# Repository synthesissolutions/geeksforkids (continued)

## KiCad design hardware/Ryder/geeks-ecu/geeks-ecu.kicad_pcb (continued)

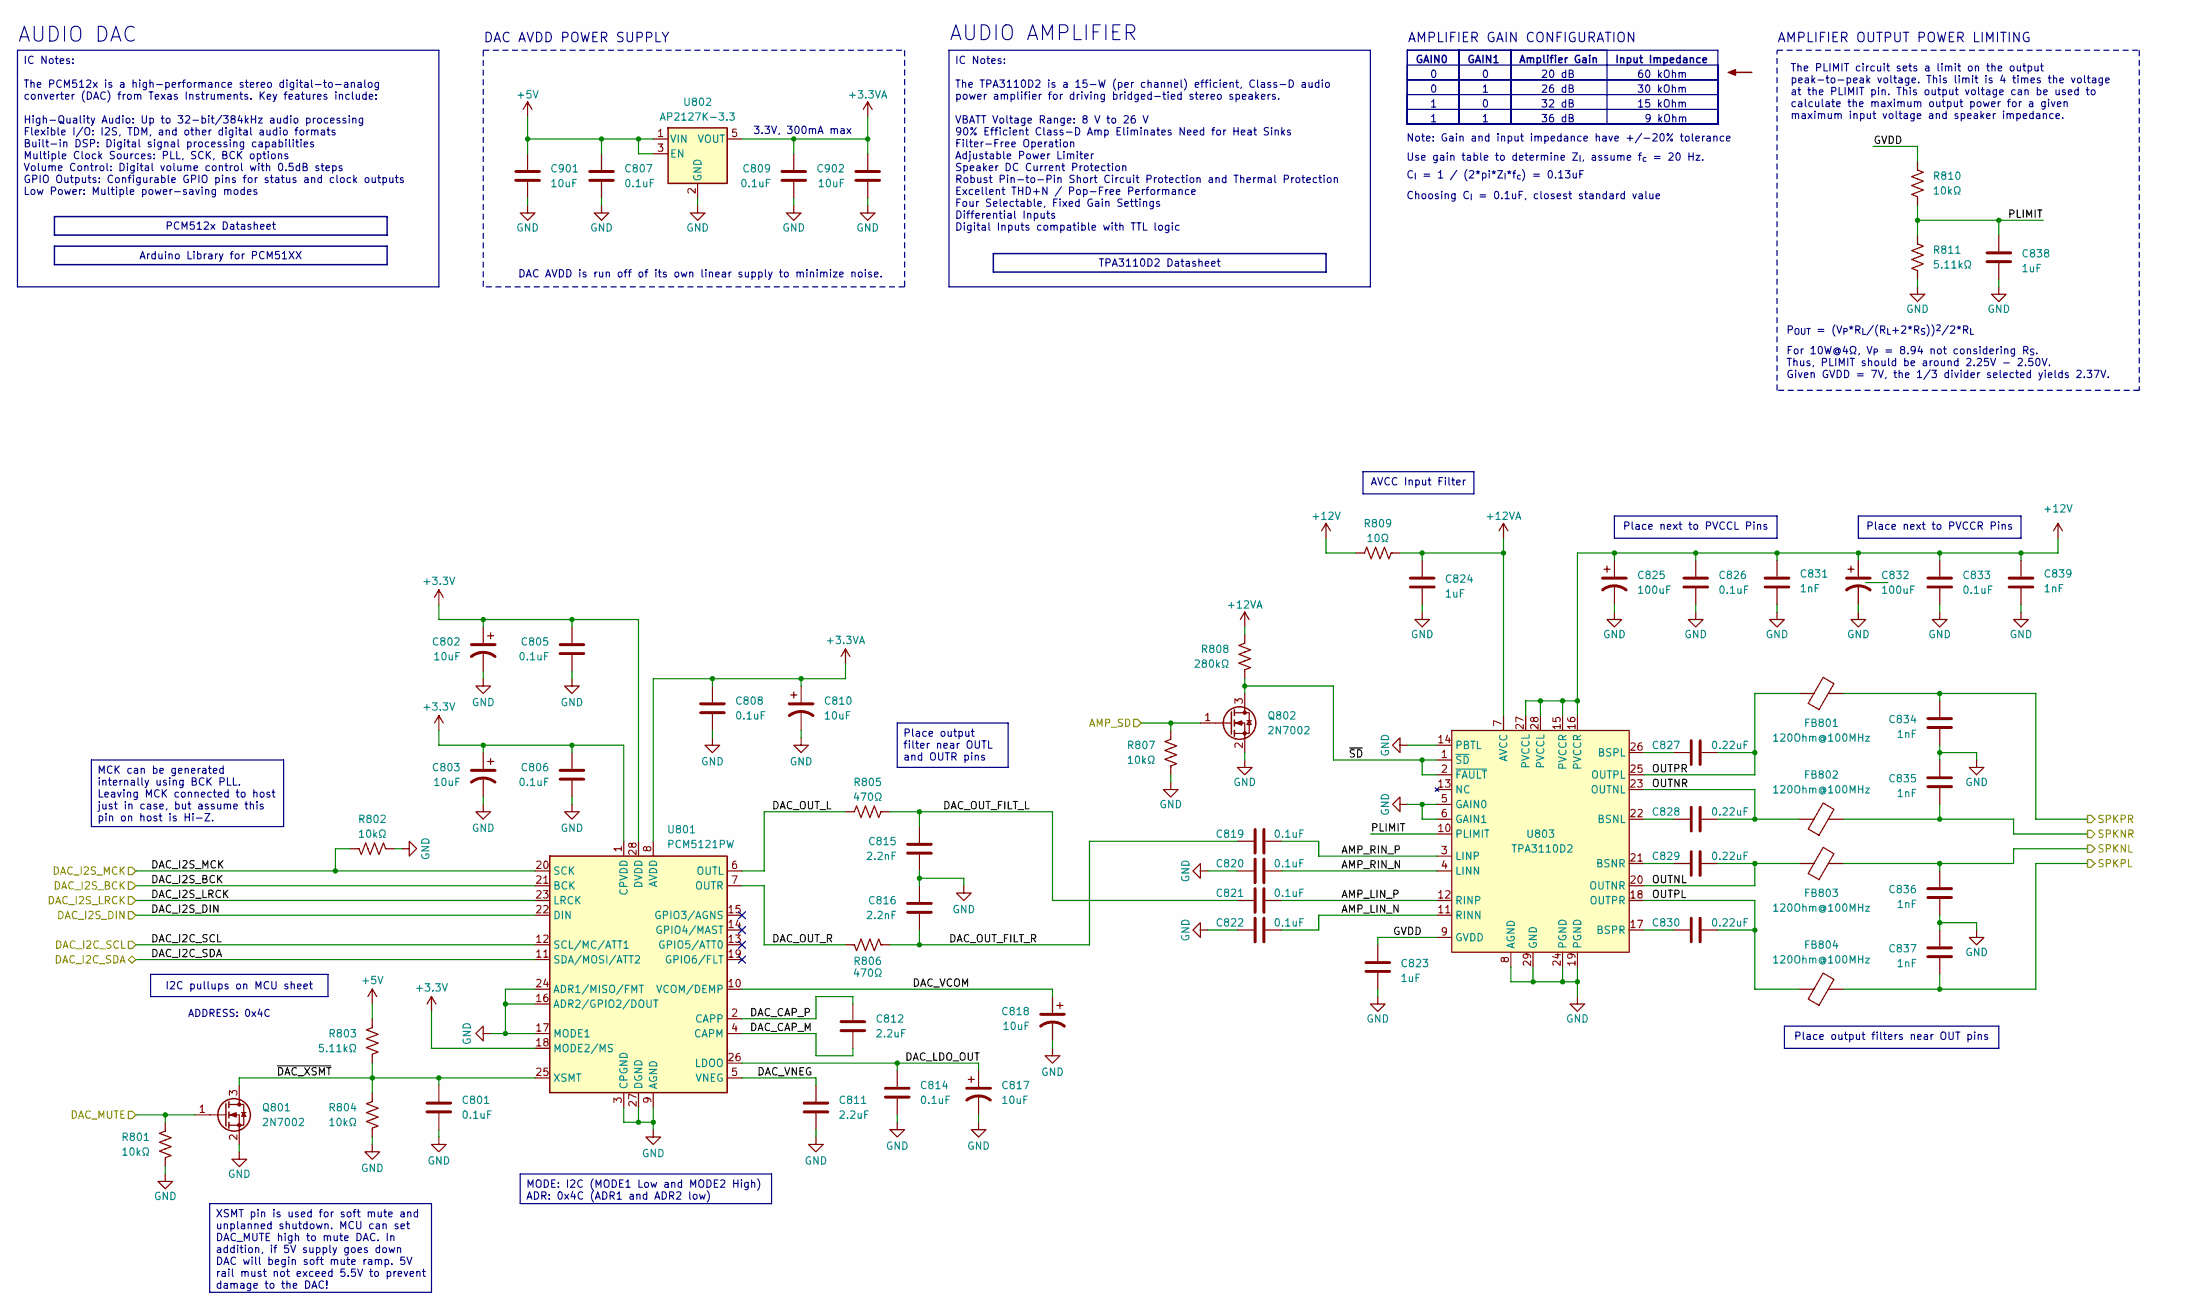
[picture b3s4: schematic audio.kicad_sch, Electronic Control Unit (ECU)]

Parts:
C801, C805, C806, C807, C808, C809, C814, C826, C833: 0.1uF; C_0603_1608Metric; MPN C14663
C802, C803, C810, C817, C818: 10uF; CP_Elec_4x5.4; MPN C72485
C811, C812: 2.2uF; C_0805_2012Metric; MPN C19110
C815, C816: 2.2nF; C_0603_1608Metric; MPN C77033
C819, C820, C821, C822: 0.1uF; C_1206_3216Metric; MPN C97946
C823, C824, C838: 1uF; C_0603_1608Metric; MPN C5199872
C825, C832: 100uF; CP_Radial_D6.3mm_P2.50mm; MPN C47891
C827, C828, C829, C830: 0.22uF; C_1206_3216Metric; MPN C464977
C831, C839: 1nF; C_0603_1608Metric; MPN C106205
C834, C835, C836, C837: 1nF; C_0603_1608Metric; MPN C77026
C901, C902: 10uF; C_0805_2012Metric; MPN C2932476
FB801, FB802, FB803, FB804: 120Ohm@100MHz; L_1206_3216Metric; MPN C3011219
Q801, Q802: 2N7002; SOT-23; MPN C22446827
R801, R802, R804, R807, R810: 10kΩ; R_0603_1608Metric; MPN C25804
R803, R811: 5.11kΩ; R_0603_1608Metric; MPN C23067
R805, R806: 470Ω; R_0603_1608Metric; MPN C23179
R808: 280kΩ; R_0603_1608Metric; MPN C22970
R809: 10Ω; R_0603_1608Metric; MPN C22859
U801: PCM5121PW; TSSOP-28_4.4x9.7mm_P0.65mm; MPN C2651652
U802: AP2127K-3.3; SOT-23-5; MPN C156285
U803: TPA3110D2; HTSSOP-28-1EP_4.4x9.7mm_P0.65mm_EP3.4x9.5mm_Mask2.4x6.17mm_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; MPN C30132

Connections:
+5V: C807.1, C901.2, R803.1, U802.1 (VIN), U802.3 (EN); also elsewhere on the board
+12V: C825.1, C826.1, C831.1, C832.1, C833.1, C839.1, R809.1, U803.15 (PVCCR), U803.16 (PVCCR), U803.27 (PVCCL), U803.28 (PVCCL); also elsewhere on the board
+12VA: C824.2, R808.1, R809.2, U803.7 (AVCC)
/AMP_SD: Q802.1 (G), R807.1; also elsewhere on the board
/Audio/AMP_LIN_N: C822.1, U803.11 (RINN)
/Audio/AMP_LIN_P: C821.1, U803.12 (RINP)
/Audio/AMP_RIN_N: C820.1, U803.4 (LINN)
/Audio/AMP_RIN_P: C819.1, U803.3 (LINP)
/Audio/DAC_CAP_M: C812.2, U801.4 (CAPM)
/Audio/DAC_CAP_P: C812.1, U801.2 (CAPP)
/Audio/DAC_I2S_MCK: R802.2, U801.20 (SCK)
/Audio/DAC_LDO_OUT: C814.1, C817.1, U801.26 (LDOO)
/Audio/DAC_OUT_FILT_L: C815.1, C821.2, R805.2
/Audio/DAC_OUT_FILT_R: C816.2, C819.2, R806.2
/Audio/DAC_OUT_L: R805.1, U801.6 (OUTL)
/Audio/DAC_OUT_R: R806.1, U801.7 (OUTR)
/Audio/DAC_VCOM: C818.1, U801.10 (VCOM/DEMP)
/Audio/DAC_VNEG: C811.1, U801.5 (VNEG)
/Audio/GVDD: C823.2, R810.1, U803.9 (GVDD)
/Audio/OUTNL: C829.1, FB803.1, U803.20 (OUTNR)
/Audio/OUTNR: C828.1, FB802.1, U803.23 (OUTNL)
/Audio/OUTPL: C830.1, FB804.1, U803.18 (OUTPR)
/Audio/OUTPR: C827.1, FB801.1, U803.25 (OUTPL)
/Audio/PLIMIT: C838.2, R810.2, R811.1, U803.10 (PLIMIT)
/Audio/~DAC_XSMT: C801.1, Q801.3 (D), R803.2, R804.1, U801.25 (XSMT)
/Audio/~SD: Q802.3 (D), R808.2, U803.1 (~SD), U803.2 (~FAULT)
/DAC_I2C_SCL: U801.12 (SCL/MC/ATT1); also elsewhere on the board
/DAC_I2C_SDA: U801.11 (SDA/MOSI/ATT2); also elsewhere on the board
/DAC_I2S_BCK: U801.21 (BCK); also elsewhere on the board
/DAC_I2S_DIN: U801.22 (DIN); also elsewhere on the board
/DAC_I2S_LRCK: U801.23 (LRCK); also elsewhere on the board
/DAC_MUTE: Q801.1 (G), R801.1; also elsewhere on the board
/SPKNL: C836.1, FB803.2; also elsewhere on the board
/SPKNR: C835.2, FB802.2; also elsewhere on the board
/SPKPL: C837.2, FB804.2; also elsewhere on the board
/SPKPR: C834.1, FB801.2; also elsewhere on the board
GND: C801.2, C802.2, C803.2, C805.2, C806.2, C807.2, C808.2, C809.2, C810.2, C811.2, C814.2, C815.2, C816.1, C817.2, C818.2, C820.2, C822.2, C823.1, C824.1, C825.2, C826.2, C831.2, C832.2, C833.2, C834.2, C835.1, C836.2, C837.1, C838.1, C839.2, C901.1, C902.1, Q801.2 (S), Q802.2 (S), R801.2, R802.1, R804.2, R807.2, R811.2, U801.3 (CPGND), U801.9 (AGND), U801.16 (ADR2/GPIO2/DOUT), U801.17 (MODE1), U801.24 (ADR1/MISO/FMT), U801.27 (DGND), U802.2 (GND), U803.5 (GAIN0), U803.6 (GAIN1), U803.8 (AGND), U803.14 (PBTL), U803.19 (PGND), U803.24 (PGND), U803.29 (GND); also elsewhere on the board
unnamed: C828.2, U803.22 (BSNL)
unnamed: C829.2, U803.21 (BSNR)
unnamed: C827.2, U803.26 (BSPL)
unnamed: C830.2, U803.17 (BSPR)

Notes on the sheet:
For 10W@4Ω, V_{P} = 8.94 not considering R_{S}. Thus, PLIMIT should be around 2.25V - 2.50V. Given GVDD = 7V, the 1/3 divider selected yields 2.37V.
30 kOhm
AMPLIFIER GAIN CONFIGURATION
AUDIO AMPLIFIER
20 dB
3.3V, 300mA max
GAIN1
Use gain table to determine Z_{I}, assume f_{c} = 20 Hz.
Input Impedance
15 kOhm
AMPLIFIER OUTPUT POWER LIMITING
DAC AVDD POWER SUPPLY
C_{I} = 1 / (2*pi*Z_{I}*f_{c}) = 0.13uF
Note: Gain and input impedance have +/-20% tolerance
DAC AVDD is run off of its own linear supply to minimize noise.
GAIN0
Amplifier Gain
ADDRESS: 0x4C
36 dB
Choosing C_{I} = 0.1uF, closest standard value
26 dB
P_{OUT} = (V_{P}*R_{L}/(R_{L}+2*R_{S}))^{2}/2*R_{L}
AUDIO DAC
60 kOhm
32 dB
9 kOhm
IC Notes: The TPA3110D2 is a 15-W (per channel) efficient, Class-D audio power amplifier for driving bridged-tied stereo speakers. VBATT Voltage Range: 8 V to 26 V 90% Efficient Class-D Amp Eliminates Need for Heat Sinks Filter-Free Operation Adjustable Power Limiter Speaker DC Current Protection R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
TPA3110D2 Datasheet
Place next to PVCCL Pins
The PLIMIT circuit sets a limit on the output peak-to-peak voltage. This limit is 4 times the voltage at the PLIMIT pin. This output voltage can be used to calculate the maximum output power for a given maximum input voltage and speaker impedance.
Place next to PVCCR Pins
MODE: I2C (MODE1 Low and MODE2 High) ADR: 0x4C (ADR1 and ADR2 low)
Arduino Library for PCM51XX
MCK can be generated internally using BCK PLL. Leaving MCK connected to host just in case, but assume this pin on host is Hi-Z.
Place output filter near OUTL and OUTR pins
PCM512x Datasheet
AVCC Input Filter
I2C pullups on MCU sheet
XSMT pin is used for soft mute and unplanned shutdown. MCU can set DAC_MUTE high to mute DAC. In addition, if 5V supply goes down DAC will begin soft mute ramp. 5V rail must not exceed 5.5V to prevent damage to the DAC!
Place output filters near OUT pins

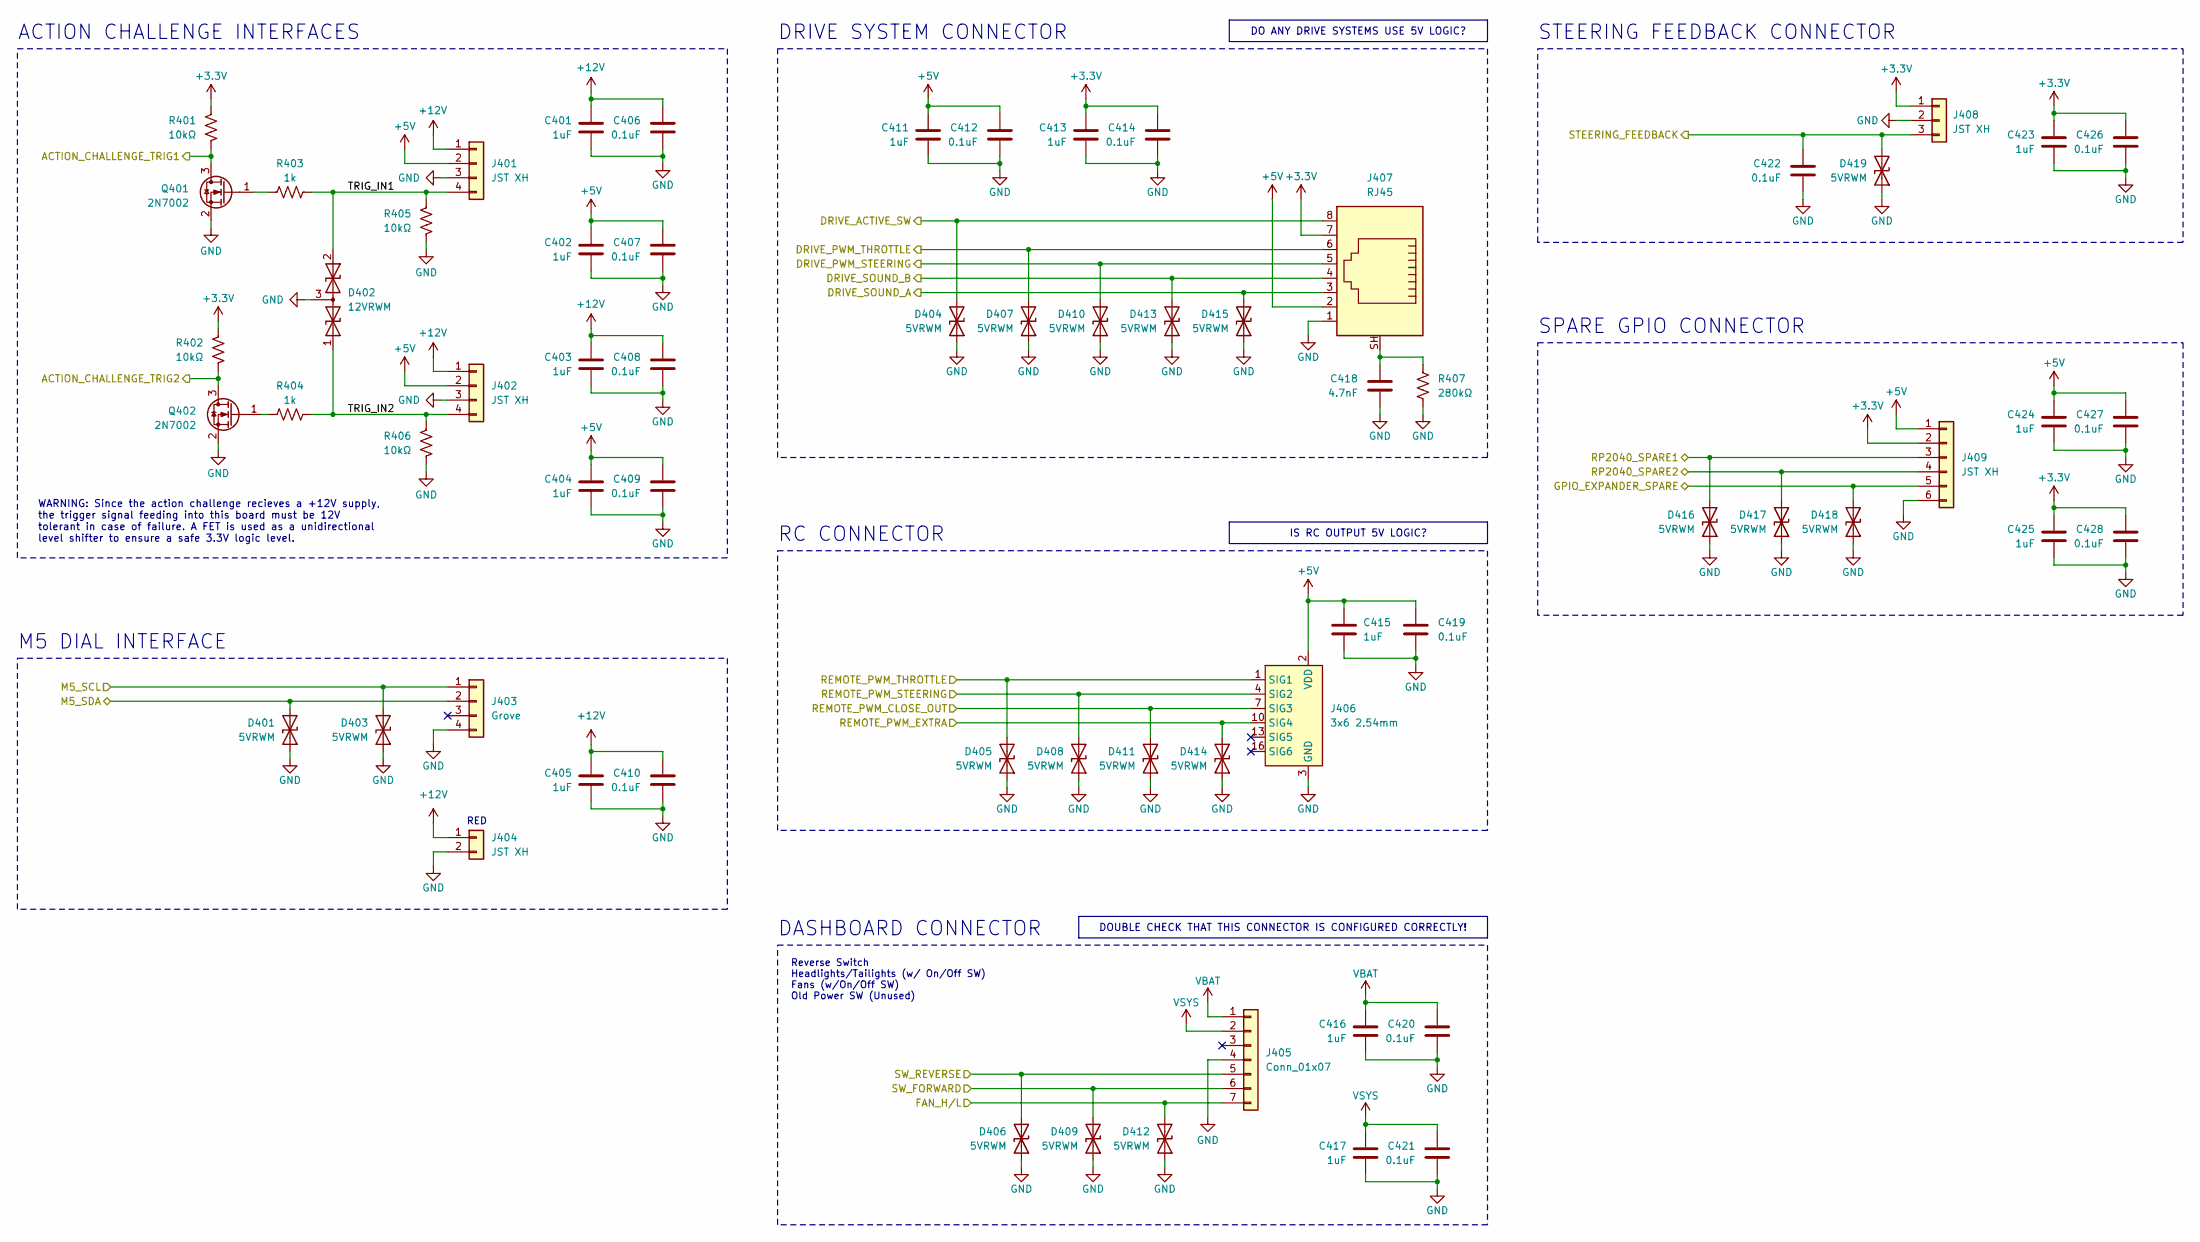
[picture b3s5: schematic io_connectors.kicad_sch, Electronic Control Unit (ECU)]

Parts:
C401, C402, C403, C404, C405, C411, C413, C415, C416, C417, C423, C424, C425: 1uF; C_0603_1608Metric; MPN C5199872
C406, C407, C408, C409, C410, C412, C414, C419, C420, C421, C422, C426, C427, C428: 0.1uF; C_0603_1608Metric; MPN C14663
C418: 4.7nF; C_0805_2012Metric; MPN C565695
D401, D403, D404, D405, D406, D407, D408, D409, D410, D411, D412, D413, D414, D415, D416, D417, D418, D419: 5VRWM; D_SOD-882; MPN C110694
D402: 12VRWM; SOT-23; MPN C32677
J401, J402: JST XH; JST_XH_B4B-XH-AM_1x04_P2.50mm_Vertical; MPN C161871
J403: Grove; NS-Tech_Grove_1x04_P2mm_Vertical; MPN 110990030
J404: JST XH; JST_XH_B2B-XH-AM_1x02_P2.50mm_Vertical; MPN C495685
J405: Conn_01x07; JST_XH_B7B-XH-AM_1x07_P2.50mm_Vertical
J406: 3x6 2.54mm; PinHeader_3x06_P2.54mm_Vertical
J407: RJ45; RJ45_Amphenol_RJHSE5380
J408: JST XH; JST_XH_B3B-XH-AM_1x03_P2.50mm_Vertical; MPN C161870
J409: JST XH; JST_XH_B6B-XH-AM_1x06_P2.50mm_Vertical; MPN C161873
Q401, Q402: 2N7002; SOT-23; MPN C8545
R401, R402, R405, R406: 10kΩ; R_0603_1608Metric; MPN C25804
R403, R404: 1k; R_0402_1005Metric; MPN C11702
R407: 280kΩ; R_0603_1608Metric; MPN C22970

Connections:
+5V: C402.2, C404.2, C407.1, C409.1, C411.2, C412.1, C415.2, C419.1, C424.2, C427.1, J401.2, J402.2, J406.2 (VDD), J406.5 (VDD), J406.8 (VDD), J406.11 (VDD), J406.14 (VDD), J406.17 (VDD), J407.2, J409.1; also elsewhere on the board
+12V: C401.2, C403.2, C405.2, C406.1, C408.1, C410.1, J401.1, J402.1, J404.1; also elsewhere on the board
/ACTION_CHALLENGE_TRIG1: Q401.3 (D), R401.2; also elsewhere on the board
/ACTION_CHALLENGE_TRIG2: Q402.3 (D), R402.2; also elsewhere on the board
/DRIVE_ACTIVE_SW: D404.2 (A2), J407.8; also elsewhere on the board
/DRIVE_PWM_STEERING: D410.2 (A2), J407.5; also elsewhere on the board
/DRIVE_PWM_THROTTLE: D407.2 (A2), J407.6; also elsewhere on the board
/DRIVE_SOUND_A: D415.2 (A2), J407.3; also elsewhere on the board
/DRIVE_SOUND_B: D413.2 (A2), J407.4; also elsewhere on the board
/FAN_H/L: D412.2 (A2), J405.7; also elsewhere on the board
/GPIO_EXPANDER_SPARE: D418.2 (A2), J409.5; also elsewhere on the board
/IO Connectors/TRIG_IN1: D402.2 (A2), J401.4, R403.2, R405.1
/IO Connectors/TRIG_IN2: D402.1 (A1), J402.4, R404.2, R406.1
/M5_SCL: D403.2 (A2), J403.1; also elsewhere on the board
/M5_SDA: D401.2 (A2), J403.2; also elsewhere on the board
/REMOTE_PWM_CLOSE_OUT: D411.2 (A2), J406.7 (SIG3); also elsewhere on the board
/REMOTE_PWM_EXTRA: D414.2 (A2), J406.10 (SIG4); also elsewhere on the board
/REMOTE_PWM_STEERING: D408.2 (A2), J406.4 (SIG2); also elsewhere on the board
/REMOTE_PWM_THROTTLE: D405.2 (A2), J406.1 (SIG1); also elsewhere on the board
/RP2040_SPARE1: D416.2 (A2), J409.3; also elsewhere on the board
/RP2040_SPARE2: D417.2 (A2), J409.4; also elsewhere on the board
/STEERING_FEEDBACK: C422.1, D419.2 (A2), J408.3; also elsewhere on the board
/SW_FORWARD: D409.2 (A2), J405.6; also elsewhere on the board
/SW_REVERSE: D406.2 (A2), J405.5; also elsewhere on the board
GND: C401.1, C402.1, C403.1, C404.1, C405.1, C406.2, C407.2, C408.2, C409.2, C410.2, C411.1, C412.2, C413.1, C414.2, C415.1, C416.1, C417.1, C418.2, C419.2, C420.2, C421.2, C422.2, C423.1, C424.1, C425.1, C426.2, C427.2, C428.2, D401.1 (A1), D402.3 (common), D403.1 (A1), D404.1 (A1), D405.1 (A1), D406.1 (A1), D407.1 (A1), D408.1 (A1), D409.1 (A1), D410.1 (A1), D411.1 (A1), D412.1 (A1), D413.1 (A1), D414.1 (A1), D415.1 (A1), D416.1 (A1), D417.1 (A1), D418.1 (A1), D419.1 (A1), J401.3, J402.3, J403.4, J404.2, J405.4, J406.3 (GND), J406.6 (GND), J406.9 (GND), J406.12 (GND), J406.15 (GND), J406.18 (GND), J407.1, J408.2, J409.6, Q401.2 (S), Q402.2 (S), R405.2, R406.2, R407.2; also elsewhere on the board
unnamed: C418.1, J407.SH, R407.1
unnamed: Q401.1 (G), R403.1
unnamed: Q402.1 (G), R404.1
VBAT: C416.2, C420.1, J405.1; also elsewhere on the board
VSYS: C417.2, C421.1, J405.2; also elsewhere on the board

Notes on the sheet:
WARNING: Since the action challenge recieves a +12V supply, the trigger signal feeding into this board must be 12V tolerant in case of failure. A FET is used as a unidirectional level shifter to ensure a safe 3.3V logic level.
RED
DASHBOARD CONNECTOR
Reverse Switch Headlights/Tailights (w/ On/Off SW) Fans (w/On/Off SW) Old Power SW (Unused)
M5 DIAL INTERFACE
SPARE GPIO CONNECTOR
ACTION CHALLENGE INTERFACES
STEERING FEEDBACK CONNECTOR
RC CONNECTOR
DRIVE SYSTEM CONNECTOR
IS RC OUTPUT 5V LOGIC?
DO ANY DRIVE SYSTEMS USE 5V LOGIC?
DOUBLE CHECK THAT THIS CONNECTOR IS CONFIGURED CORRECTLY!

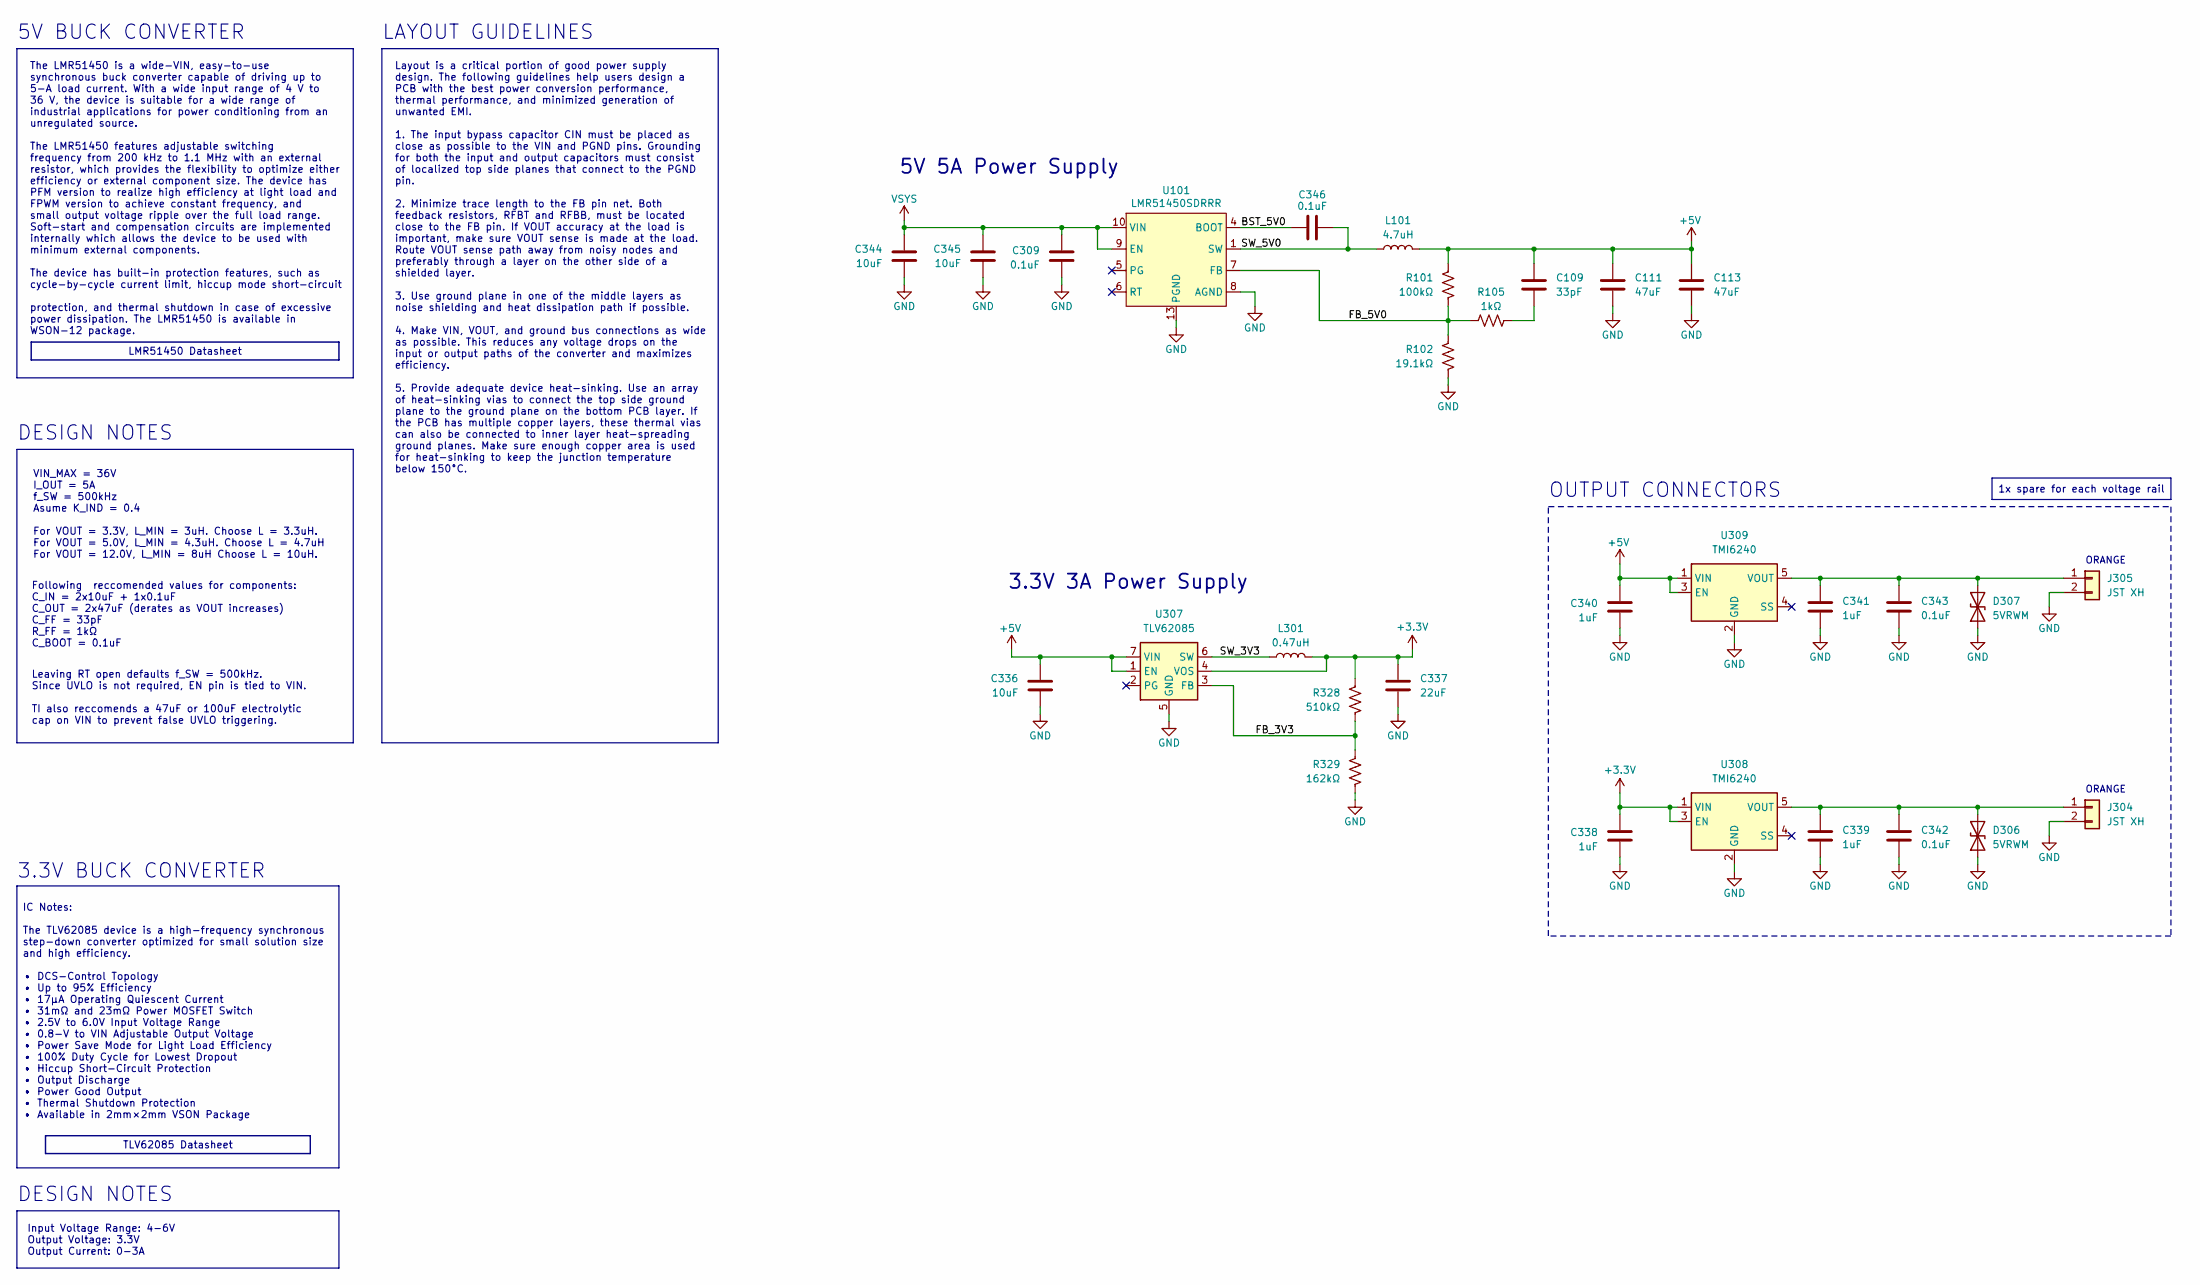
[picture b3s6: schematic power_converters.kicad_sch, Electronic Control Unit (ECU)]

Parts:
C109: 33pF; C_0402_1005Metric; MPN C107005
C111, C113: 47uF; C_1210_3225Metric; MPN C7432791
C309, C342, C343, C346: 0.1uF; C_0603_1608Metric; MPN C14663
C336, C344, C345: 10uF; C_0805_2012Metric; MPN C2932476
C337: 22uF; C_0805_2012Metric; MPN C98190
C338, C339, C340, C341: 1uF; C_0603_1608Metric; MPN C5199872
D306, D307: 5VRWM; D_SOD-882; MPN C110694
J304, J305: JST XH; JST_XH_B2B-XH-AM_1x02_P2.50mm_Vertical; MPN C495547
L101: 4.7uH; L_TechFuse_SL1050; MPN C22463842
L301: 0.47uH; L_1008_2520Metric; MPN C5832368
R101: 100kΩ; R_0402_1005Metric; MPN C25741
R102: 19.1kΩ; R_0402_1005Metric; MPN C52036
R105: 1kΩ; R_0402_1005Metric; MPN C11702
R328: 510kΩ; R_0603_1608Metric; MPN C23192
R329: 162kΩ; R_0603_1608Metric; MPN C22815
U101: LMR51450SDRRR; WSON-12-1EP_3x3mm_P0.5mm_EP1.5x2.5mm_ThermalVias; MPN C6890985
U307: TLV62085; RLT0007A; MPN C477932
U308, U309: TMI6240; SOT-23-5; MPN C2979914

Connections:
+5V: C109.1, C111.1, C113.1, C336.2, C340.2, L101.2, R101.1, U307.1 (EN), U307.7 (VIN), U309.1 (VIN), U309.3 (EN); also elsewhere on the board
/Low Voltage Power Converters/BST_5V0: C346.1, U101.4 (BOOT)
/Low Voltage Power Converters/FB_3V3: R328.2, R329.1, U307.3 (FB)
/Low Voltage Power Converters/FB_5V0: R101.2, R102.1, R105.1, U101.7 (FB)
/Low Voltage Power Converters/SW_3V3: L301.1, U307.6 (SW)
/Low Voltage Power Converters/SW_5V0: C346.2, L101.1, U101.1 (SW), U101.2 (SW), U101.3 (SW)
GND: C111.2, C113.2, C309.2, C336.1, C337.1, C338.1, C339.1, C340.1, C341.1, C342.2, C343.2, C344.1, C345.1, D306.1 (A1), D307.1 (A1), J304.2, J305.2, R102.2, R329.2, U101.8 (AGND), U101.13 (PGND), U307.5 (GND), U308.2 (GND), U309.2 (GND); also elsewhere on the board
unnamed: C109.2, R105.2
unnamed: C339.2, C342.1, D306.2 (A2), J304.1, U308.5 (VOUT)
unnamed: C341.2, C343.1, D307.2 (A2), J305.1, U309.5 (VOUT)
VSYS: C309.1, C344.2, C345.2, U101.9 (EN), U101.10 (VIN), U101.11 (VIN), U101.12 (VIN); also elsewhere on the board

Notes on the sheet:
DESIGN NOTES
5V 5A Power Supply
3.3V BUCK CONVERTER
5V BUCK CONVERTER
OUTPUT CONNECTORS
Input Voltage Range: 4-6V Output Voltage: 3.3V Output Current: 0-3A
ORANGE
Following reccomended values for components: C_IN = 2x10uF + 1x0.1uF C_OUT = 2x47uF (derates as VOUT increases) C_FF = 33pF R_FF = 1kΩ C_BOOT = 0.1uF
Leaving RT open defaults f_SW = 500kHz. Since UVLO is not required, EN pin is tied to VIN. TI also reccomends a 47uF or 100uF electrolytic cap on VIN to prevent false UVLO triggering.
VIN_MAX = 36V I_OUT = 5A f_SW = 500kHz Asume K_IND = 0.4 For VOUT = 3.3V, L_MIN = 3uH. Choose L = 3.3uH. For VOUT = 5.0V, L_MIN = 4.3uH. Choose L = 4.7uH For VOUT = 12.0V, L_MIN = 8uH Choose L = 10uH.
LAYOUT GUIDELINES
3.3V 3A Power Supply
IC Notes: The TLV62085 device is a high-frequency synchronous step-down converter optimized for small solution size and high efficiency. • DCS-Control Topology • Up to 95% Efficiency • 17μA Operating Quiescent Current • 31mΩ and 23mΩ Power MOSFET Switch • 2.5V to 6.0V Input Voltage Range • 0.8-V to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
LMR51450 Datasheet
Layout is a critical portion of good power supply design. The following guidelines help users design a PCB with the best power conversion performance, thermal performance, and minimized generation of unwanted EMI. 1. The input bypass capacitor CIN must be placed as close as possible to the VIN and 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
1x spare for each voltage rail
The LMR51450 is a wide-VIN, easy-to-use synchronous buck converter capable of driving up to 5-A load current. With a wide input range of 4 V to 36 V, the device is suitable for a wide range of industrial applications for power conditioning from an unregulated source. The LMR51450 features adjustabl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
TLV62085 Datasheet

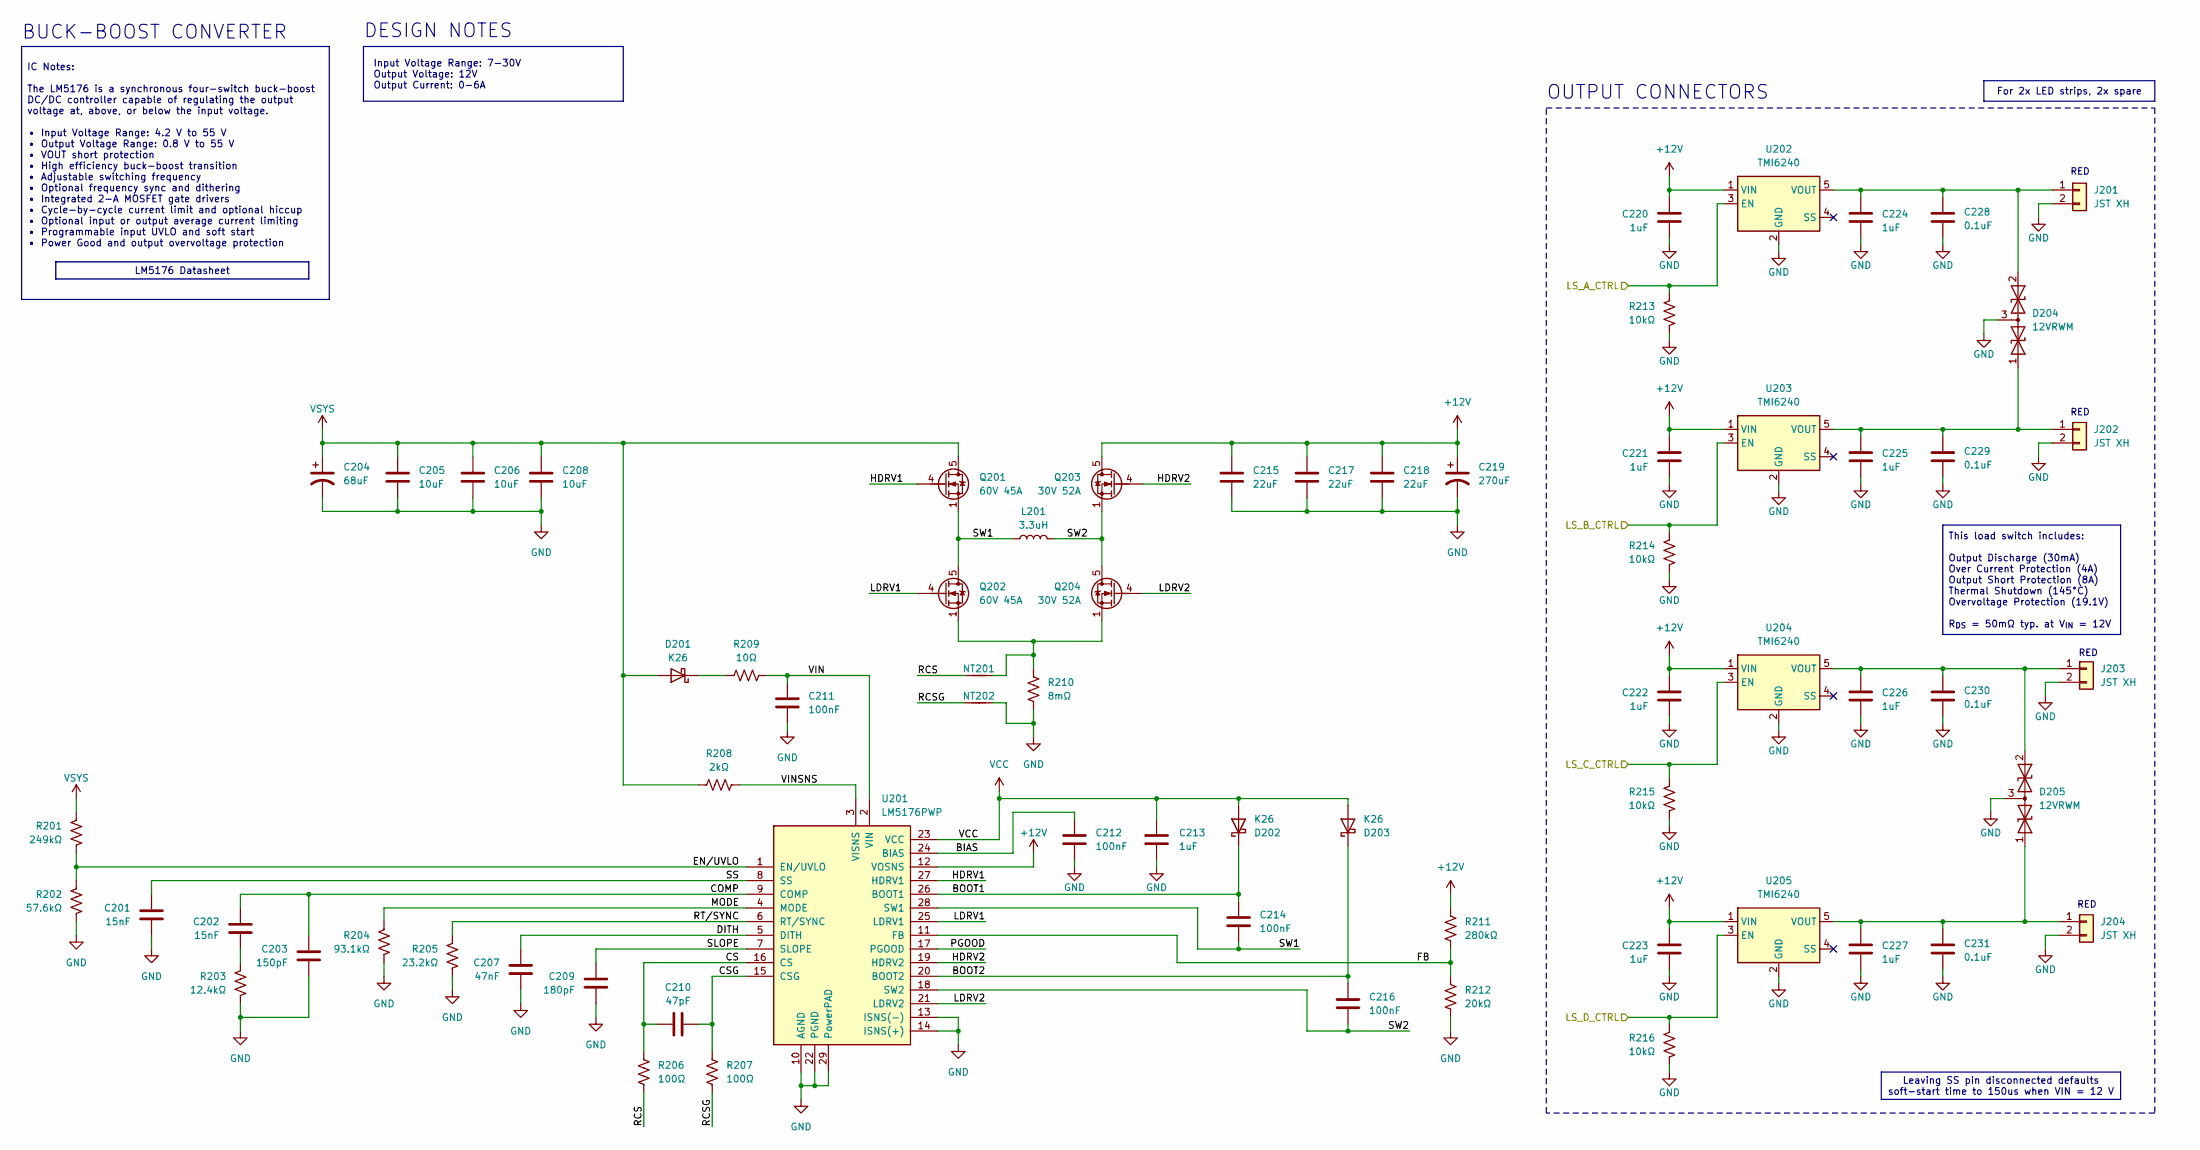
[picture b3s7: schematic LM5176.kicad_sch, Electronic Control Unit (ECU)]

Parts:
C201, C202: 15nF; C_0603_1608Metric; MPN C696363
C203: 150pF; C_0603_1608Metric; MPN C107038
C204: 68uF; CP_Elec_8x10; MPn C46528111
C205, C206, C208: 10uF; C_0805_2012Metric; MPN C2932476
C207: 47nF; C_0603_1608Metric; MPN C1622
C209: 180pF; C_0603_1608Metric; MPN C107041
C210: 47pF; C_0603_1608Metric; MPN C513324
C211, C212, C214, C216: 100nF; C_0603_1608Metric; MPN C14663
C213, C220, C221, C222, C223, C224, C225, C226, C227: 1uF; C_0603_1608Metric; MPN C5199872
C215, C217, C218: 22uF; C_0805_2012Metric; MPN C5677683
C219: 270uF; CP_Elec_8x10; MPn C2161621
C228, C229, C230, C231: 0.1uF; C_0603_1608Metric; MPN C14663
D201, D202, D203: K26; D_SOD-123F; MPN C2922179
D204, D205: 12VRWM; SOT-23; MPN C32677
J201, J202, J203, J204: JST XH; JST_XH_B2B-XH-AM_1x02_P2.50mm_Vertical; MPN C495685
L201: 3.3uH; L_APV_APH1265; MPN C5349636
NT201, NT202: NetTie_2; NetTie-2_SMD_Pad0.5mm
Q201, Q202: 60V 45A; PQFN-8-EP_6x5mm_P1.27mm_Generic; MPN C41354975
Q203, Q204: 30V 52A; PQFN-8-EP_6x5mm_P1.27mm_Generic; MPN C508835
R201: 249kΩ; R_0603_1608Metric; MPN C22918
R202: 57.6kΩ; R_0603_1608Metric; MPN C23082
R203: 12.4kΩ; R_0603_1608Metric; MPN C22865
R204: 93.1kΩ; R_0603_1608Metric; MPN C23266
R205: 23.2kΩ; R_0603_1608Metric; MPN C23346
R206, R207: 100Ω; R_0603_1608Metric; MPN C22775
R208: 2kΩ; R_0603_1608Metric; MPN C22975
R209: 10Ω; R_0603_1608Metric; MPN C109318
R210: 8mΩ; R_2512_6332Metric; MPN C509729
R211: 280kΩ; R_0603_1608Metric; MPN C22970
R212: 20kΩ; R_0603_1608Metric; MPN C4184
R213, R214, R215, R216: 10kΩ; R_0603_1608Metric; MPN C25804v
U201: LM5176PWP; HTSSOP-28-1EP_4.4x9.7mm_P0.65mm_EP3.4x9.5mm_ThermalVias; MPN C442493
U202, U203, U204, U205: TMI6240; SOT-23-5; MPN C2979914

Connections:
+12V: C215.1, C217.1, C218.1, C219.1, C220.2, C221.2, C222.2, C223.2, Q203.5 (D), R211.1, U201.12 (VOSNS), U202.1 (VIN), U203.1 (VIN), U204.1 (VIN), U205.1 (VIN); also elsewhere on the board
/12V Buck-Boost Converter/BIAS: C212.1, U201.24 (BIAS)
/12V Buck-Boost Converter/BOOT1: C214.1, D202.1 (K), U201.26 (BOOT1)
/12V Buck-Boost Converter/BOOT2: C216.1, D203.1 (K), U201.20 (BOOT2)
/12V Buck-Boost Converter/COMP: C202.1, C203.1, U201.9 (COMP)
/12V Buck-Boost Converter/CS: C210.1, R206.1, U201.16 (CS)
/12V Buck-Boost Converter/CSG: C210.2, R207.1, U201.15 (CSG)
/12V Buck-Boost Converter/DITH: C207.1, U201.5 (DITH)
/12V Buck-Boost Converter/EN/UVLO: R201.2, R202.1, U201.1 (EN/UVLO)
/12V Buck-Boost Converter/FB: R211.2, R212.1, U201.11 (FB)
/12V Buck-Boost Converter/HDRV1: Q201.4 (G), U201.27 (HDRV1)
/12V Buck-Boost Converter/HDRV2: Q203.4 (G), U201.19 (HDRV2)
/12V Buck-Boost Converter/LDRV1: Q202.4 (G), U201.25 (LDRV1)
/12V Buck-Boost Converter/LDRV2: Q204.4 (G), U201.21 (LDRV2)
/12V Buck-Boost Converter/MODE: R204.1, U201.4 (MODE)
/12V Buck-Boost Converter/PGOOD: U201.17 (PGOOD)
/12V Buck-Boost Converter/RCS: NT201.1, R206.2
/12V Buck-Boost Converter/RCSG: NT202.1, R207.2
/12V Buck-Boost Converter/RT/SYNC: R205.1, U201.6 (RT/SYNC)
/12V Buck-Boost Converter/SLOPE: C209.1, U201.7 (SLOPE)
/12V Buck-Boost Converter/SS: C201.1, U201.8 (SS)
/12V Buck-Boost Converter/SW1: C214.2, L201.1, Q201.1 (S), Q201.2 (S), Q201.3 (S), Q202.5 (D), U201.28 (SW1)
/12V Buck-Boost Converter/SW2: C216.2, L201.2, Q203.1 (S), Q203.2 (S), Q203.3 (S), Q204.5 (D), U201.18 (SW2)
/12V Buck-Boost Converter/VIN: C211.1, R209.2, U201.2 (VIN)
/12V Buck-Boost Converter/VINSNS: R208.2, U201.3 (VISNS)
/LS_A_CTRL: R213.1, U202.3 (EN); also elsewhere on the board
/LS_B_CTRL: R214.1, U203.3 (EN); also elsewhere on the board
/LS_C_CTRL: R215.1, U204.3 (EN); also elsewhere on the board
/LS_D_CTRL: R216.1, U205.3 (EN); also elsewhere on the board
GND: C201.2, C203.2, C204.2, C205.1, C206.1, C207.2, C208.1, C209.2, C211.2, C212.2, C213.1, C215.2, C217.2, C218.2, C219.2, C220.1, C221.1, C222.1, C223.1, C224.1, C225.1, C226.1, C227.1, C228.2, C229.2, C230.2, C231.2, D204.3 (common), D205.3 (common), J201.2, J202.2, J203.2, J204.2, NT202.2, R202.2, R203.2, R204.2, R205.2, R210.2, R212.2, R213.2, R214.2, R215.2, R216.2, U201.10 (AGND), U201.13 (ISNS(-)), U201.14 (ISNS(+)), U201.22 (PGND), U201.29 (PowerPAD), U202.2 (GND), U203.2 (GND), U204.2 (GND), U205.2 (GND); also elsewhere on the board
unnamed: C202.2, R203.1
unnamed: D201.1 (K), R209.1
unnamed: C225.2, C229.1, D204.1 (A1), J202.1, U203.5 (VOUT)
unnamed: C224.2, C228.1, D204.2 (A2), J201.1, U202.5 (VOUT)
unnamed: C227.2, C231.1, D205.1 (A1), J204.1, U205.5 (VOUT)
unnamed: C226.2, C230.1, D205.2 (A2), J203.1, U204.5 (VOUT)
unnamed: NT201.2, Q202.1 (S), Q202.2 (S), Q202.3 (S), Q204.1 (S), Q204.2 (S), Q204.3 (S), R210.1
VCC: C213.2, D202.2 (A), D203.2 (A), U201.23 (VCC)
VSYS: C204.1, C205.2, C206.2, C208.2, D201.2 (A), Q201.5 (D), R201.1, R208.1; also elsewhere on the board

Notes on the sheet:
RED
BUCK-BOOST CONVERTER
DESIGN NOTES
Input Voltage Range: 7-30V Output Voltage: 12V Output Current: 0-6A
OUTPUT CONNECTORS
IC Notes: The LM5176 is a synchronous four-switch buck-boost DC/DC controller capable of regulating the output voltage at, above, or below the input voltage. • Input Voltage Range: 4.2 V to 55 V • Output Voltage Range: 0.8 V to 55 V • VOUT short protection • High efficiency buck-boost transition • 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
Leaving SS pin disconnected defaults soft-start time to 150us when VIN = 12 V
For 2x LED strips, 2x spare
This load switch includes: Output Discharge (30mA) Over Current Protection (4A) Output Short Protection (8A) Thermal Shutdown (145°C) Overvoltage Protection (19.1V) R_{DS} = 50mΩ typ. at V_{IN} = 12V
LM5176 Datasheet

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
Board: 4 copper layers, 386 parts (134 on the bottom side), 205 nets, no tracks yet.

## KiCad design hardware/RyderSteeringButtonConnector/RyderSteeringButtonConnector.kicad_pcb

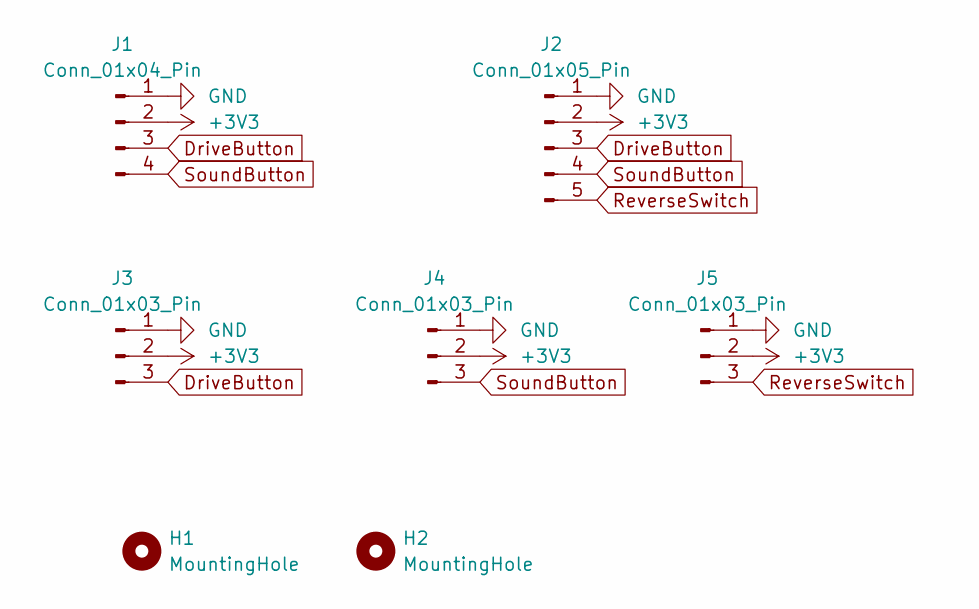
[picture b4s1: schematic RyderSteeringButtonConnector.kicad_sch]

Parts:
H1, H2: MountingHole; MountingHole_2.7mm_M2.5
J1: Conn_01x04_Pin; JST_SH_SM04B-SRSS-TB_1x04-1MP_P1.00mm_Horizontal; LCSC Part # C160403
J2: Conn_01x05_Pin; JST_SH_SM05B-SRSS-TB_1x05-1MP_P1.00mm_Horizontal; LCSC Part # C136657
J3, J4, J5: Conn_01x03_Pin; JST_SH_BM03B-SRSS-TB_1x03-1MP_P1.00mm_Vertical; LCSC Part # C160389

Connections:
+3V3: J1.2, J2.2, J3.2, J4.2, J5.2
DriveButton: J1.3, J2.3, J3.3
GND: J1.1, J2.1, J3.1, J4.1, J5.1
ReverseSwitch: J2.5, J5.3
SoundButton: J1.4, J2.4, J4.3
